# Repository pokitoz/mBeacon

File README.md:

# mBeacon

## Antenna

- No angle on the trace
- Vias should surround the track and the antenna to apply a shielding
- It is best to avoid the use FR4 stack layer
  - As this is not controled and epsilon can vary. 
  - HR370 isola is better to control the impedence

To check the 50Ohm, use the too AppCAD or https://saturnpcb.com/saturn-pcb-toolkit/
- Go to `Tools > DRC...` 
- find layer stack in eagle..
- copper is selected when ordering. Check the manufacturer webite: https://jlcpcb.com/capabilities/Capabilities
- stack manager: Isolation height and copper height Track height.

## Manufacturing

- File > Generate CAM data
  - Export to .zip and upload to manufacturing site
- For jlcpcb, BOM and CPL needs to be generated: https://support.jlcpcb.com/article/132-how-to-generate-bom-and-cpl-from-eagle-cad-automatically

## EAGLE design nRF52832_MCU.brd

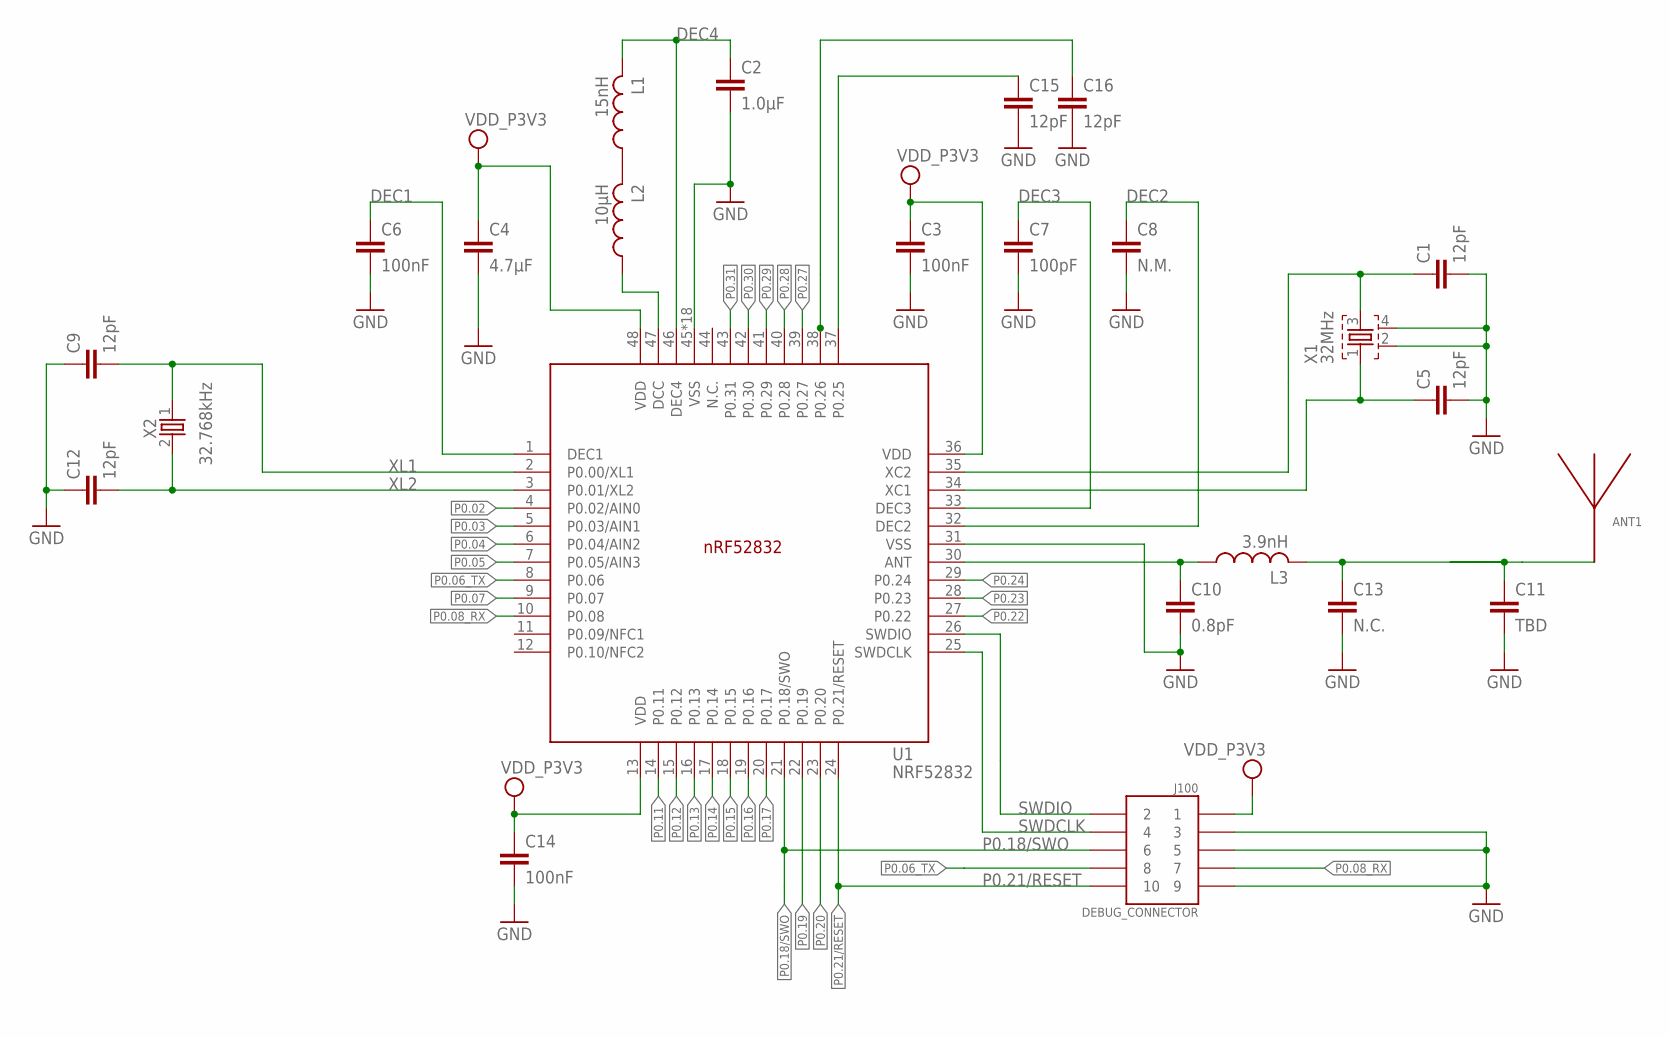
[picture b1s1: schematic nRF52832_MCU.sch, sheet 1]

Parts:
ANT1: ANTENNA_QUARTER-WAVE_MONOPOLE_MEANDERED_LEFT; QWMP_MEANDERED_LEFT_+6
C1, C5, C9, C12, C15, C16: 12pF; RESC0402_N
C2: 1.0µF; RESC0603_N
C3, C6, C14: 100nF; RESC0402_N
C4: 4.7µF; RESC0603_N
C7: 100pF; RESC0402_N
C8: N.M.; RESC0402_N
C10: 0.8pF; RESC0402_N
C11: TBD; RESC0402_N
C13: N.C.; RESC0402_N
J100: DEBUG_CONNECTOR; HDRV127P5X2-10_N
L1: 15nH; RESC0402_N
L2: 10µH; RESC0603_N
L3: 3.9nH; RESC0402_N
U1: NRF52832; QFN40P600X600X90-48_N
X1: 32MHz; BT-XTAL_2016_N
X2: 32.768kHz; XTAL_3215_N

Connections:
ANT: C10.1, L3.1, U1.30 (ANT)
DEC1: C6.1, U1.1 (DEC1)
DEC2: C8.1, U1.32 (DEC2)
DEC3: C7.1, U1.33 (DEC3)
DEC4: C2.1, L1.2, U1.46 (DEC4)
unnamed: L1.1, L2.2
unnamed: C1.1, U1.35 (XC2), X1.3
unnamed: L2.1, U1.47 (DCC)
unnamed: ANT1.P$1, C11.1, C13.1, L3.2
unnamed 14: C1.2, C2.2, C3.2, C4.2, C5.2, C6.2, C7.2, C8.2, C9.1, C10.2, C11.2, C12.1, C13.2, C14.2, C15.2, C16.2, J100.3, J100.5, J100.9, U1.31 (VSS), U1.45 (VSS), U1.PAD (VSS), U1.PAD@VIA01 (VSS), U1.PAD@VIA02 (VSS), U1.PAD@VIA03 (VSS), U1.PAD@VIA04 (VSS), U1.PAD@VIA05 (VSS), U1.PAD@VIA06 (VSS), U1.PAD@VIA07 (VSS), U1.PAD@VIA08 (VSS), U1.PAD@VIA09 (VSS), U1.PAD@VIA10 (VSS), U1.PAD@VIA11 (VSS), U1.PAD@VIA12 (VSS), U1.PAD@VIA13 (VSS), U1.PAD@VIA14 (VSS), U1.PAD@VIA15 (VSS), U1.PAD@VIA16 (VSS), X1.2, X1.4; also elsewhere on the board
P0.02: U1.4 (P0.02/AIN0)
P0.03: U1.5 (P0.03/AIN1)
P0.04: U1.6 (P0.04/AIN2); also elsewhere on the board
P0.05: U1.7 (P0.05/AIN3); also elsewhere on the board
P0.06_TX: J100.8, U1.8 (P0.06)
P0.07: U1.9 (P0.07); also elsewhere on the board
P0.08_RX: J100.7, U1.10 (P0.08)
P0.11: U1.14 (P0.11)
P0.12: U1.15 (P0.12)
P0.13: U1.16 (P0.13); also elsewhere on the board
P0.14: U1.17 (P0.14); also elsewhere on the board
P0.15: U1.18 (P0.15)
P0.16: U1.19 (P0.16)
P0.17: U1.20 (P0.17)
P0.18/SWO: J100.6, U1.21 (P0.18/SWO)
P0.19: U1.22 (P0.19)
P0.20: U1.23 (P0.20)
P0.21/RESET: J100.10, U1.24 (P0.21/RESET)
P0.22: U1.27 (P0.22)
P0.23: U1.28 (P0.23)
P0.24: U1.29 (P0.24)
P0.25: C15.1, U1.37 (P0.25)
P0.26: C16.1, U1.38 (P0.26)
P0.27: U1.39 (P0.27)
P0.28: U1.40 (P0.28)
P0.29: U1.41 (P0.29)
P0.30: U1.42 (P0.30)
P0.31: U1.43 (P0.31)
SWDCLK: J100.4, U1.25 (SWDCLK)
SWDIO: J100.2, U1.26 (SWDIO)
VDD_P3V3: C3.1, C4.1, C14.1, J100.1, U1.13 (VDD), U1.36 (VDD), U1.48 (VDD); also elsewhere on the board
X1: C5.1, U1.34 (XC1), X1.1
XL1: C9.2, U1.2 (P0.00/XL1), X2.1
XL2: C12.2, U1.3 (P0.01/XL2), X2.2

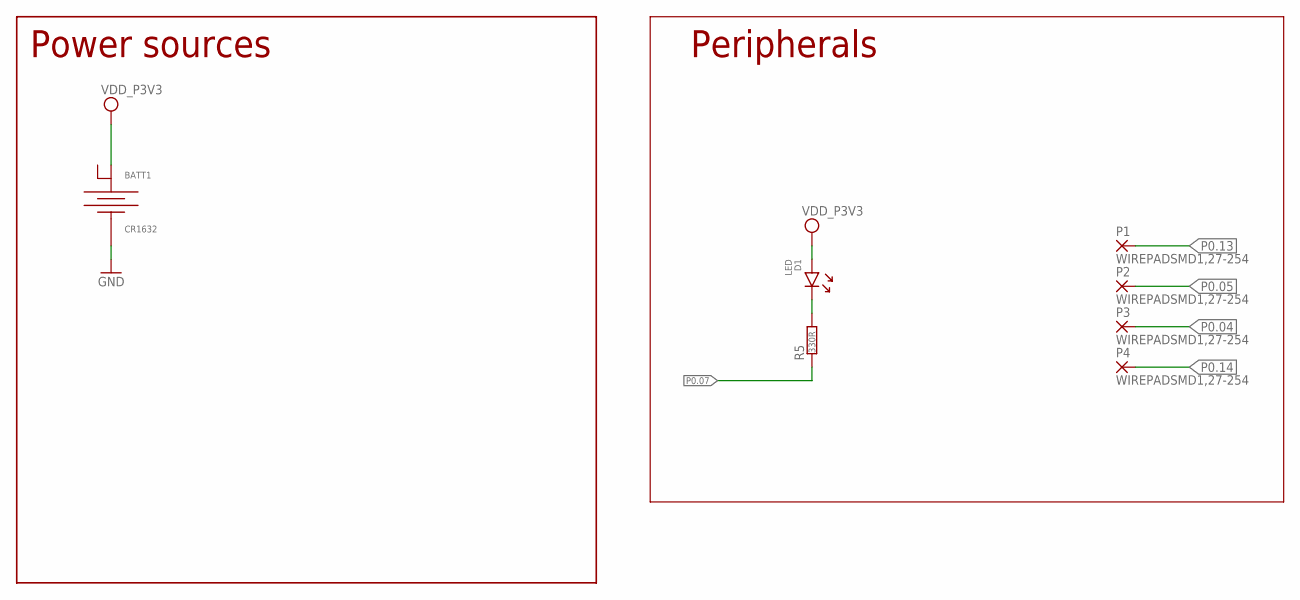
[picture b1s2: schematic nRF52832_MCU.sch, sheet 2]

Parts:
BATT1: CR1632; CR1632_HOLDER_TH
D1: LED; DIOC0603_N
P1, P2, P3, P4: WIREPADSMD1,27-254; SMD1,27-2,54
R5: 330R; RESC0402_N

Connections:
unnamed: D1.1 (C), R5.2
unnamed 14: BATT1.1 (-); also elsewhere on the board
P0.04: P3.1; also elsewhere on the board
P0.05: P2.1; also elsewhere on the board
P0.07: R5.1; also elsewhere on the board
P0.13: P1.1; also elsewhere on the board
P0.14: P4.1; also elsewhere on the board
VDD_P3V3: BATT1.2 (+), D1.2 (A); also elsewhere on the board

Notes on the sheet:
Power sources
Peripherals

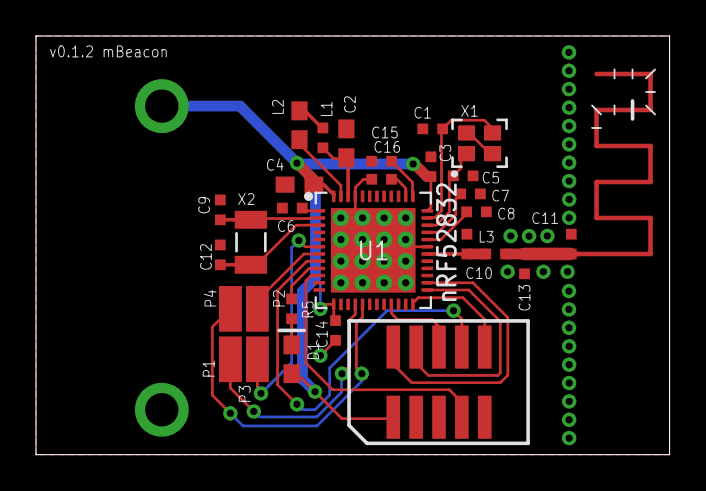
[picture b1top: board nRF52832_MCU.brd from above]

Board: 2 copper layers, 35.2 x 23.3 mm, 31 parts (1 on the bottom side), 28 nets.

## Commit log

2021-12-20 Add first design eagle mBeacon
2021-12-20 Add missing capacitors
2021-12-21 Update rastnest
2021-12-21 Add info on PCB antenna trace
2021-12-21 Add additional pin connector
2021-12-21 Fix warnings on layout
2021-12-28 Antenna airwire without detour
2021-12-28 Update dec capacitor orrientation
2021-12-28 Update labels and restrict masks
2021-12-28 Remove DRC errors
2021-12-29 Add board version
2021-12-29 Add space for further devices
    Accelerometer, pressure,..
2021-12-29 Make sure rastnest is around battery
2021-12-29 Add instruction for BOM and jlcpcb
2021-12-29 Same size signal for antenna link
2021-12-29 Add coplanar computation
2022-01-15 Add main.c
2022-01-15 Updated nrf52 board for mBeacon board
2022-01-15 Add CONFIG
2022-01-15 Add archive
2022-01-15 Add Readme
2022-01-15 Add platform IO sources
2022-01-18 Add flags for using internal crystal
2022-01-18 Add warning on space in the PATH
2023-06-18 Add eagle update
